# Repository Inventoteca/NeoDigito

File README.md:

<h1> NeoDigito </h1>

NeoDigito are seven-segment displays, RGB Color and one pin control. This is the Arduino library for controll it. 

Support us on Kickstarter

https://www.kickstarter.com/projects/neodigitos/neodigito-modular-7-segment-rgb-display

Based on ws2812b controller aka Adafruit_NeoPixel.

<h2>Installing</h2>
After downloading both libraries Adafruit_NeoPixel and this, rename folder to 'NeoDigito' and 'Adafruit_NeoPixel', and  and install in Arduino Libraries folder. Restart Arduino IDE, then open File->Sketchbook->Library->NeoDigito->hello sketch.

<h3>Features</h3>
- Arduino, easy to use, print('1234');
- Free: GNU 3.0
- One pin control
- 16 millions of colors

Functions
- begin()
- print()
- show()
- clear()
- setColor()
- setCursor()
- updateColor()
- updateDelimiter()
- updatePoint()
- updateTilde()
- updateDigitType()
- updatePixType()
- setPin()

First arguments of colors 0-17 are reservet for colors and effects.

Examples

There are many examples implemented in this library. One of the examples is below. You can find other examples here

Work In Progress:
- Colors FX's
- Customize the order of segments
- Control brigness
- Alphanumeric

About Us
This project is a tribute to Iván Ríos de Paz, friend, maker and a great person. We miss you.

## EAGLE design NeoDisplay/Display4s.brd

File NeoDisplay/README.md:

Display hecho de 4 displays de 7 segmentos basados en NeoPixel

Archivos de esquematico y placa en Eagle para el diseño de pcb,
para poder alimentar y reprogramar ESP 01 sin necesidad de extraer la tapa.

El circuito consta de un convertidor de micro USB a serial, un ESP 01, 2 botones y pines machos y hembras,
es importante tomar en cuenta el diseño del display para el orden y dimenciones del circuito

La primera versión consta de una placa perforada para circuito, sin embargo el tamaño tan ancho no permitia
que este se pudiera cerrar.

La segunda versión fue rediseñada en Eagle para realizarse en router para pcb de esta manera se puede ahorrar espacio,
lo que nos permite que el display no sea tan ancho, dando como resultado un diseño mas compacto.

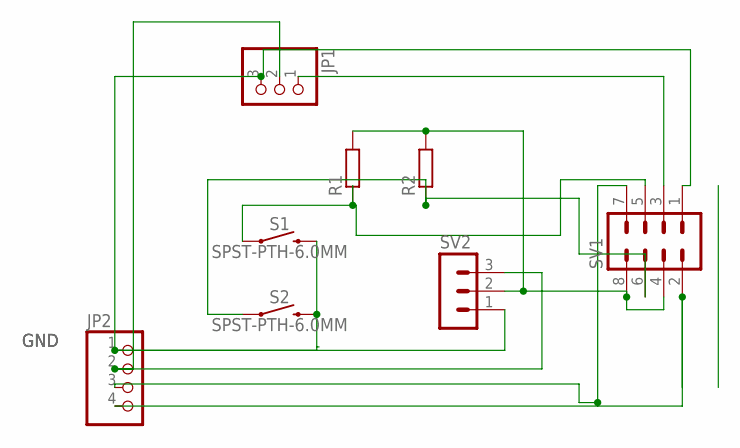
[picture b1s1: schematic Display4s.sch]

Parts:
JP1: PINHD-1X3; 1X03
JP2: PINHD-1X4; 1X04
R1, R2: R-EU_0207/10; 0207/10
S1, S2: SPST-PTH-6.0MM; TACTILE_SWITCH_PTH_6.0MM
SV1: MA04-2
SV2: MA03-1

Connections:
3V3: R1.2, R2.2, SV1.4, SV1.8, SV2.2
5V: JP1.2, JP2.2, SV2.3
FLASH: R1.1, S1.1, SV1.5
GND: JP1.3, JP2.1, S1.3 (2), S2.3 (2), SV1.1, SV2.1
RESET: R2.1, S2.1, SV1.6
RX: JP2.3, SV1.7
SING: JP1.1, SV1.3
TX: JP2.4, SV1.2

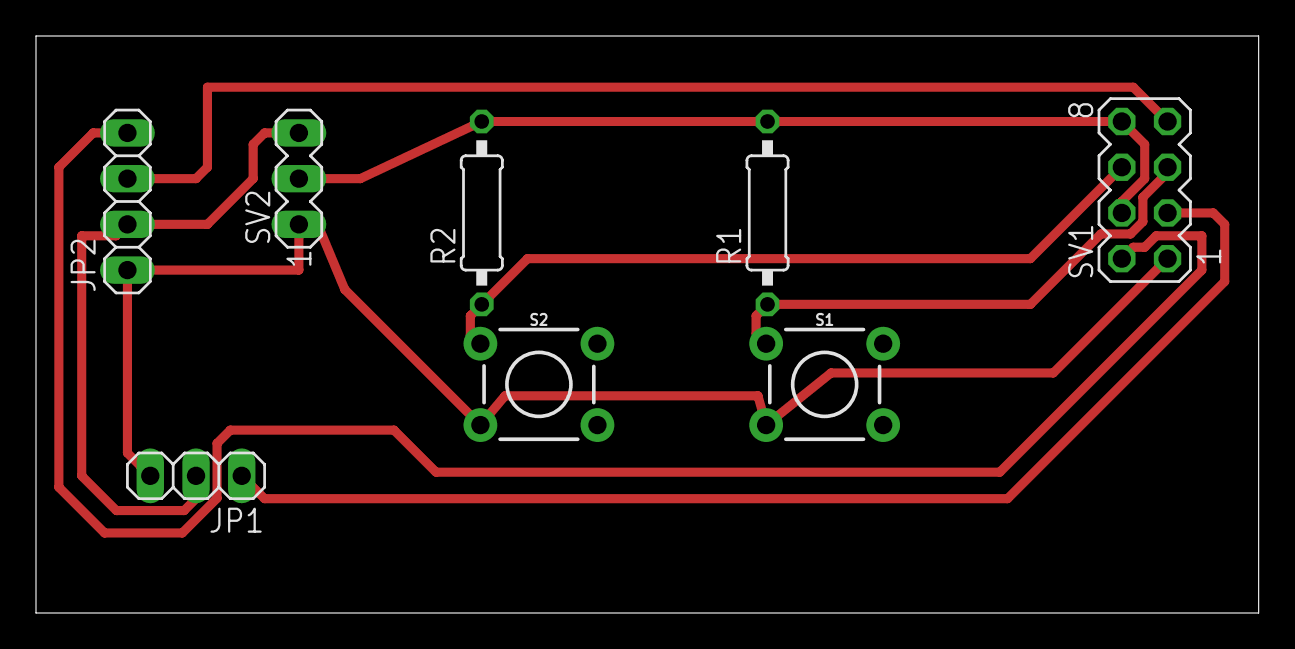
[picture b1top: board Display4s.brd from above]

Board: 2 copper layers, 67.9 x 32.1 mm, 8 parts (0 on the bottom side), 8 nets.

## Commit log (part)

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2020-10-21 Primer respaldo
    Basado en
    Seven Segment Pixel
    by Peter Hartmann
2020-10-21 Se modificó el orden de los segmentos y se agregó el pixel inicial y final, falta hacer más pruebas y correcciones a los ejemplos
2020-10-21 Modifiqué los ejemplos para que funcionen con la librería
2020-10-21 Modifiqué correctamente los nombres por NeoDigito
2020-10-22 Edité los ejemplos para coincidir con el desarrollo
2020-10-22 Revert "Merge remote-tracking branch 'NeoDigito/main' into Dev"
    This reverts commit ccf1e339bbe614cb045f55c5e364ea23481eba82.
2020-10-22 Modifiqué las librerías y el ejemplo para quitar datos extras de los espaciadores, debido a que los NeoDigitos tienen el punto al inicio y al final de cada display para poder formar los dos puntos, a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
2020-10-22 Agregué la función "print" para simplificar el envío de ingormación así como su ejemplo
2020-10-23 Arreglé la librería para que funcione con multiples displays correctamente y dejé un ejemplo único
2020-10-23 Actualicé la función write y ejemplo
    Write ahora escribe a un display en específico, actualicé el ejemplo. Print intentaré que haga las diferentes formas de enviar el dato
2020-10-23 Funciones auxiliares
    Agregué las funciones auxuliares para enviar el argumento del color del display separado o junto al dato a escribir
2020-10-23 Red is default color
2020-10-23 Version Revisada
    Version 0.1.0 Revisada
2020-10-23 Agregué displya show para poder escribir y mostrar separado
    Esto para poder mostrar la información más rápidamente
2021-06-11 Empecé Readme en Español
2021-06-12 contador en español
    Cambié el ejemplo del contador a español
2021-06-12 Revisión, inicializacón correcta
    Se revisó las librerías para iniciar la cantidad de neopixels correctos
2021-06-12 write simplificado
    Se puede usar la librería enviando solo el valor a escribir como un valor entero, falta que se distinga el signo negativo e implementar toda la función de print para aceptar los caracteres de textro
2021-06-16 update delimeter y print corregidas
    Se actualizó el ejemplo del conteo regresivo para mostrar el delimitador y la función de print pero realmente no hay diferencia aun entre print y write, solo que la acepta y funciona igual
2021-06-16 ejemplos funcionales
    Revisión de ejemplos para hacerlos funcionales
2021-06-21 Display invertido
    Giré la conexión de los neopixel y el modo en que se despliegan, empezando ahora por el más significativo
2021-06-21 Nueva función print
    ahora puedo seleccionar a partír de que display debo escribir void NeoDigito::print(int32_t num, uint16_t x)
2021-06-21 Ejemplos y librería estables
2021-06-21 funcional
2021-06-22 Tabla de letra con estructura iniciada, sin conisderar delimitador
2021-06-22 Tabla ASCII lista con mayusculas y signos
    Se empiezan a combinar letras con puntos para formar mejores caracteres
2021-06-22 Revisón de letras
    El signo de interrogación fue corregido
2021-06-22 Complementación de letras y signos
    Agregué los símbolos desde el '[' (91ascii) hasta 's' (115ascii), algunos son representados como sus mayúsculas.
2021-06-24 Tabla ASCII: Diferenciación de símbolos
    Se agregaron puntos a algunos símbolos para distinguirlos de otras letras.
2021-06-24 Modificación del ejemplo neodigito_letras
    Es una propuesta para la impresión de letras en la tira de displays: el código manda a imprimir en dos espacios cuando el número es de dos dígitos, y en tres espacios cuando ya son mayores a 99. Agre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
2021-06-25 Letras de dos espacios
    Agregué código para que imprima letras y símbolos como la 'M', 'm', 'W', 'w' y '+' en dos espacios. A las m's les agregué puntos para distinguirlas de n's individuales.
2021-06-25 Corrección de letra W
2021-06-25 Revert "Corrección de letra W"
    This reverts commit b7d9f59fbe1f4698a01ab1013812030a93c6b4d9.
2021-06-25 Tilde revisada para compilar con esp
    Se escribio el valor numérico para evitar confusiones con el compilar con el ESP
2021-06-26 Corrección en la escritura de algunas letras
    Cuando se escribían letras en dos espacios, lo impreso en el segundo espacio no se borraba, por lo que le agregué una especie de inicialización: ahora primero limpia el espacio a partir del cual se v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
2021-06-28 Estandarización de argumentos en 'write()'
    Se modificó la posición de los argumentos de la función 'write()' para que primero se inserte el número o carácter y luego la posición.
2021-06-28 Modificación de función 'write()'
    Se pasaron las condiciones para escribir letras con puntos y demás a la función 'write()' omitiendo el uso de 'print(char,int)'. Presenta errores en la escritura de letras y el ejemplo del reloj no c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
2021-06-30 Simplificación de funciones 'write()'
    La función principal es 'write(dígito,posición,rojo,verde,azul)' y las otras solo la mandan a llamar completando los argumentos faltantes
2021-06-30 Corrección de funciones 'write()' y 'print()'
    La función 'write()' se limita a escribir en un solo espacio y 'print()' hace el corrimiento para imprimir números, aún no imprime letras. Los ejemplos fueron adaptados a los cambios de estas funcion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
2021-07-01 Diseños en formato eagle
2021-07-01 Función de escritura de palabras y de flotantes
    Sobrecargué la función 'print()' para que pueda escribir palabras completas en el display o números con punto decimal. Para este último hice un pequeño ejemplo para mostrar el resultado, pero aun pue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
2021-07-02 unidos
    unido main revisado y archivos de PCB
2021-07-02 Corrección de punto decimal
    Implementación de función 'clear()', los números flotantes están restringidos a dos decimales.
2021-07-03 ejemplo mqtt
    ejemplo de mqtt con PubSubClient funcional, a un servido abierto
2021-07-03 mqtt color
    Agregué un topico para cambiar color, falta hacer que la librería tenga la capacidad de poder cambiar el color solamente, usando el getpixel color de adafruit
2021-07-04 color independiente
    la función del color permite cambiar el color independeintemente de lo que se encuentre escrito
2021-07-04 color
    el cambio de color puede ser independiente y eahora evita borrar el texto si el color el 0 o negro
2021-07-04 omite caracteres ascii extendidos
    No ejecuta nada con los extendidos del ascii, tambi{en ahora imprime la ip en el ejemplo del esp8266
2021-07-05 Control de color con tres potenciómetros
    Preparé el ejemplo donde se muestra el valor del color en hexadecimal en el display.
2021-07-05 Correción de ejemplo 3pots
    Se corrigieron errores de escritura. Se probó en Arduino Mega y funciona.
2021-07-05 Corrección de ejemplo ADC
    El ejemplo ADC solo cambia del color rojo al verde mostrando el valor del adc en el display. El ejemplo Wheel (renombrado) oscila desde el color rojo recorriendo el azul y verde hasta terminar nuevam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
2021-07-07 Ascii extendido
    Agregué los caracteres de la tabla extendida de ASCII pero no se logran imprimir. Al compilar ejemplo de letras para Arduino Uno advierte inestabilidad por falta de memoria.
2021-07-07 Optimización del enmascaramiento de letras
    'characterMap' fue convertido a byte para ocupar menos espacio de la memoria dinámica. Se omite ASCII extendido.
2021-07-07 Escritura del signo de grados
    Escribe un guion bajo en lugar de los símbolos de ASCII extendido, pero sí contempla el signo de grados. La escritura de grados con la función 'print()' añade un espacio extra.
2021-07-07 Corregido doble espacio del signo grados
    Cuando la función 'write()' detecta caracteres fuera del rango de imprimibles, regresa sin mover el cursor.
2021-07-14 Función 'wheel()'
    Implementación de función 'wheel()' para que facilite el uso de efectos de color. Se implementó una versión de función de 'colorFX()' pero no ha funcionado, se debe revisar.
2021-07-16 Efecto 'rainbow'
    Se omitió la función 'wheel()' y en su lugar se creó la función 'updatePixelColor()' que pretende actualizar el diseño y color del display sin remover el texto escrito. 'setPixelcolor()' se deja como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
2021-07-16 Efecto 'random'
    El efecto 'random' colorea cada led de un color aleatorio. Se vuelve a utilizar la función 'wheel()'. Se modificó la forma de representar la letra 't'
2021-07-16 Efectos de 'Xmas' y 'Halloween'
    Los efectos encienden leds individuales de un color distintivo de la festividad. En caso de que no se escriba correctamente algún efecto, los leds se encenderán de blanco.
2021-07-16 Simplificación de 'updatePixelColor()'
    Se optimizó la evaluación del argumento de 'updatePixelColor()'. Se modificaron los efectos de 'Xmas' y 'Halloween' para que muestre colores distintivos en gradiente.
2021-07-16 'updatePixelColor()' también sirve para colores sólidos
    Ahora la función 'updatePixelColor()' funciona tanto para poner efectos de colores, colores sólidos mediante su nombre (solo algunos) o mediante su número hexadecimal.
2021-07-16 Sobrecarga de constructor
    Al constructor también se le puede especificar la cantidad de delimitadores así como la cantidad de pixeles que contenga en caso de que el display tenga un número diferente al default (2 delimitadore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
2021-07-19 Subo ejemplo que configura datos por WiFi Manager
2021-07-19 Descripciones de código
    Se completaron las descripciones y fueron traducidas a inglés.
2021-07-19 Corrección de librería y más descripciones
2021-07-19 Corrección de efecto 'random'
    Ahora asigna un color aleatorio a cada dígito, ya no a cada pixel
2021-07-19 corrección red SSID
2021-07-21 Completado de descripciones
2021-07-21 Suscripcion a topicos generales para controlar más de un neodisplay
2021-09-03 Notas sobre la version de ArduinoJson que se ocupa
2021-09-03 Corrección versión correcta
2021-09-25 Archivos de pcb de NeoDisplay
2021-10-07 Escritura de puntos o comas seguidas ya agrega espacio
    Antes no se podía mandar una String de puros puntos ("..." por ejemplo) porque se escribían en un mismo lugar y parecía que solo se escribía uno
2021-10-07 Sobrecarga de constructores para delimitadores
    Ya se puede configurar el color de los delimitadores de múltiples formas.
2021-10-07 Compilación para ESP corregida
    ya compila el encabezado "Neodigito.h", se cambió de una arreglo de punteros a byte a un arreglo de bytes
2021-10-07 setPixelColor() admite colores por su nombre
2021-10-08 Efecto Xmas modificado
    El display cambia de color rojo a blanco. Aún falta mejorarlo
2021-10-08 Efecto de Halloween dinámico
    Los colores naranja y morado se desplazan en el display
2021-10-08 Escribir comas, dos puntos, etc deja espacio cuando son varios seguidos
    Se había solo aplicado para los puntos pero ahora también aplica para las comas, punto y coma, doble punto y apóstrofe.
2021-10-08 Condición del espacio extra en print() corregida
2021-10-08 Inicio de agrupación de pixeles en segmentos
    Se generaron 2 estructuras Digito y Segmento que permite agrupar los leds en segmentos y segmentos en digitos para un control de leds más intuitivo y mejorar el mantenimiento
2021-10-12 cambio en la estructura Digito
    * únicamente se agregó 1 comentario
2021-12-07 Moved to NeoDisplay repository
2021-12-08 Hello Example
2021-12-11 Depurando
    Acomodo de información para requisito oficial Arduino
2022-01-10 Revision compatibilidad con ESP8266
    Se agregaron llaves en los casos para poder compilar correctamente
2022-08-31 Inicializacion correcta para mas de 256 neopixels
    El tipo de variable para crear la tira de leds "n", estaba de 8 bits, se paso a 32
2022-08-31 Print sin argumento de posición
    Se usa un cursor para identificar la posisción de lo que se debe imprimir y después, con show se muestra y reinicia la posición del cursor
2022-09-01 print actualizada
    ahora se puede enviar el color y la posiscion como argumento, parece que es mejor idea no usar la posicion en la funcion y quedar solo con lo que s emanda y el color, en r,g,b o 0xfffffff, toda la pa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
2022-09-01 Ajuste para posicion automatica
    se quitaron los argumentos para enviar la posición a escribir en la función, ahora se usa setCursor para la posición y se le da prioridad al color, también se removieron las funciones relacionadas co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
2023-01-07 Preparing for share
2023-01-07 keywords
2023-01-07 readme
2023-01-07 examples ok
2023-01-07 1.0.2
2023-01-29 compatibility firebase
2023-02-11 example wifi_clock
2023-07-31 neoclock example
    Lite neoclock version
2023-08-01 New version of board ESP8266
2023-08-01 ascci ext
2023-08-02 Brightness and ASCII ext
    Ascii extende WIP, brig is ready, auto show
2023-08-03 auto show
    print also show

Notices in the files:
parts and their libraries:
SparkFun-Switches: Licensing: Creative Commons ShareAlike 4.0 International - https://creativecommons.org/licenses/by-sa/4.0
